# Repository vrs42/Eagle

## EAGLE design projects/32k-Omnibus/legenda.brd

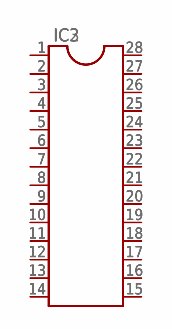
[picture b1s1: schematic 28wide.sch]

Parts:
IC2: DIL28; DIL28-6
IC3: DIL28-3

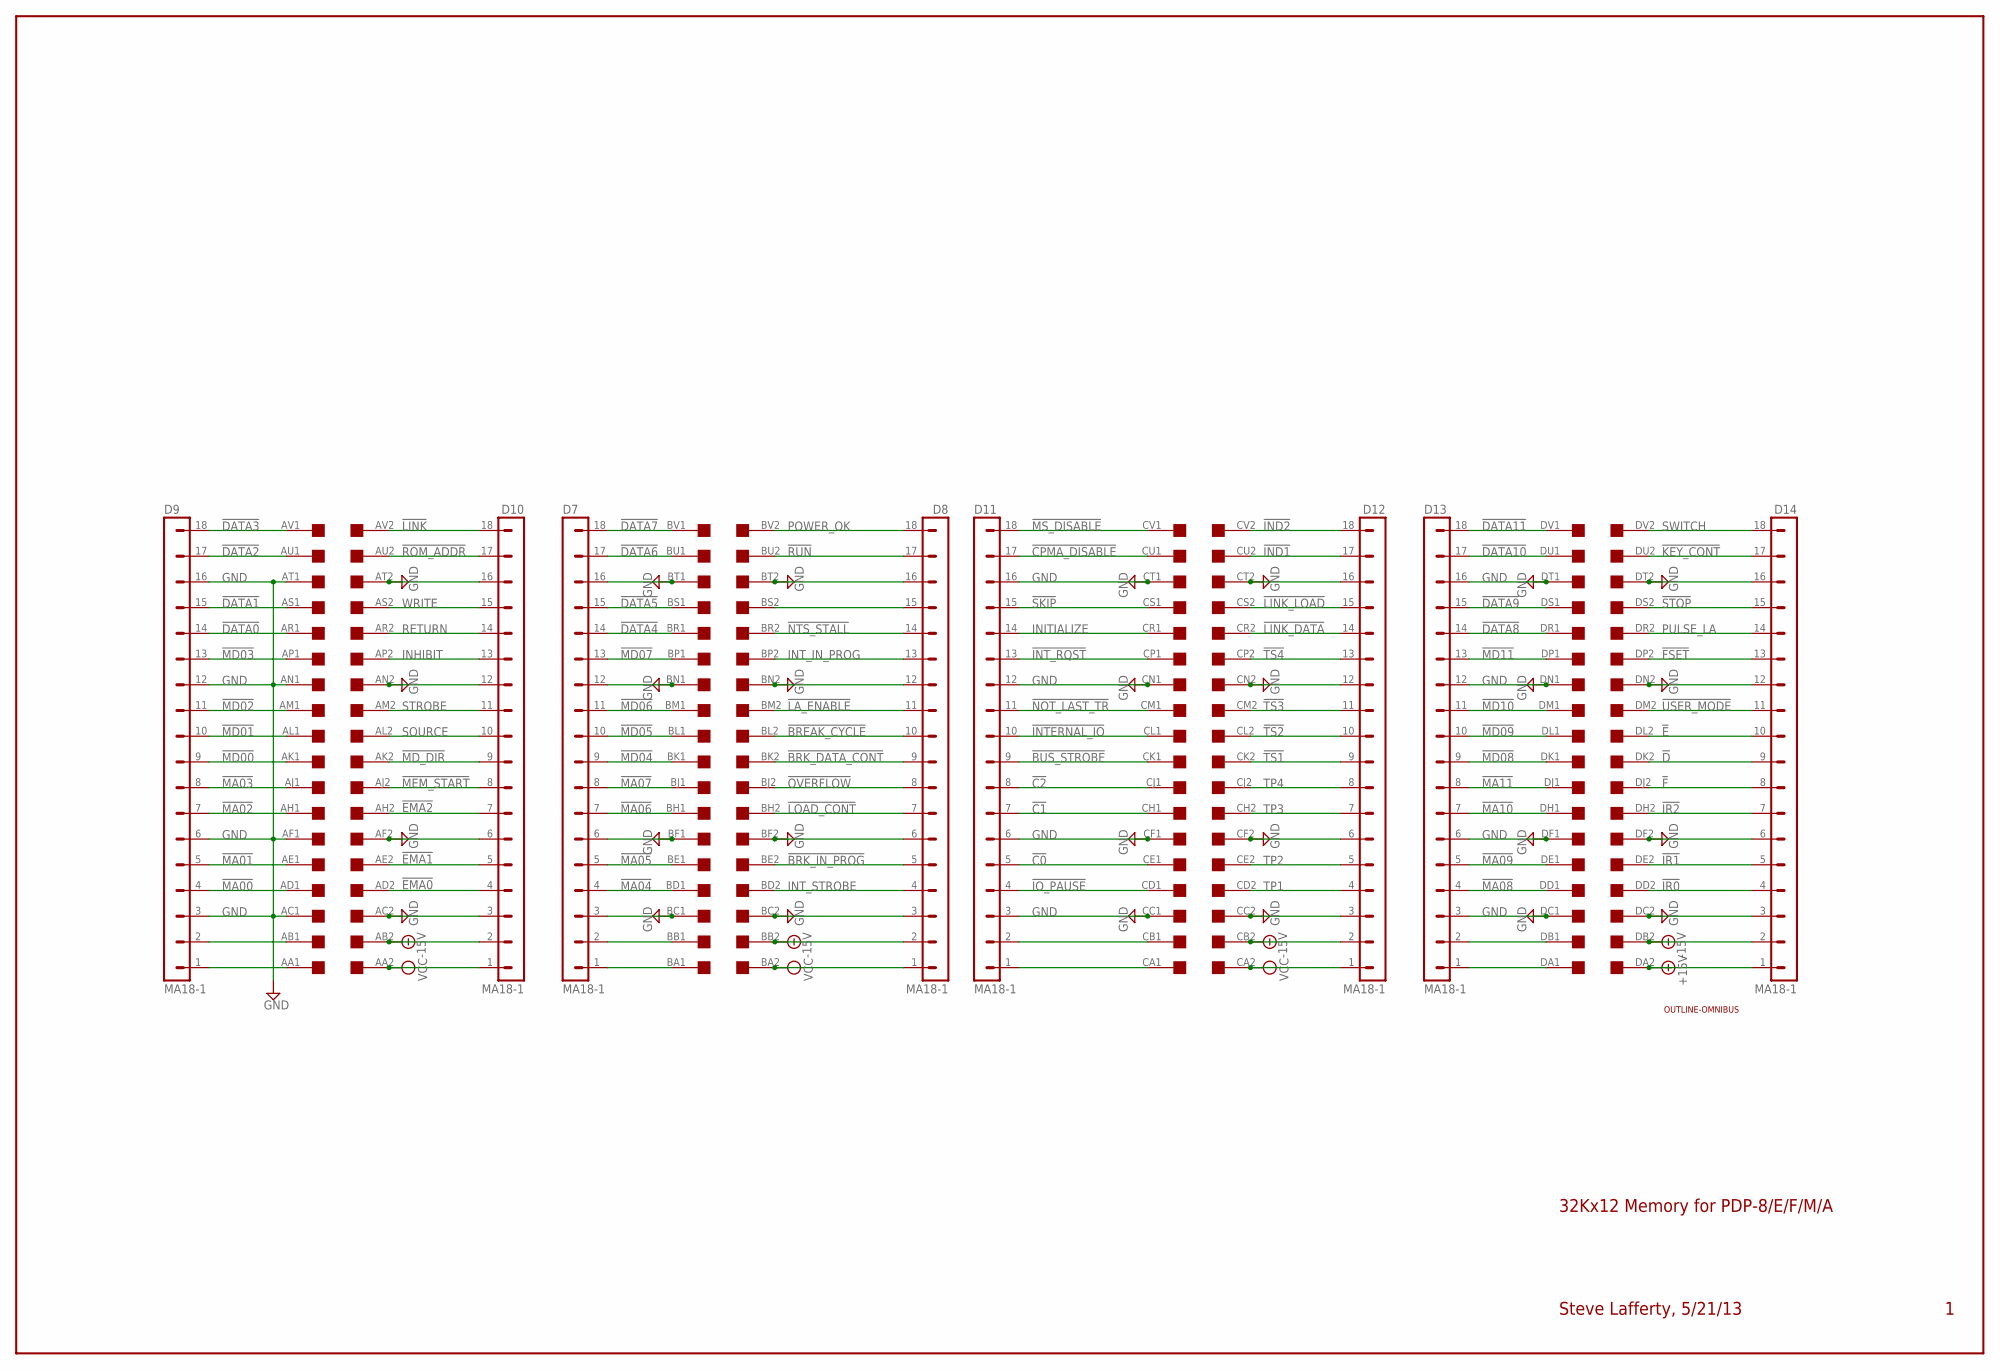
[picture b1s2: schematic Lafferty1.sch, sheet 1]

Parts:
D7, D8, D9, D10, D11, D12, D13, D14: MA18-1
U$1: OUTLINE-OMNIBUS; OMNIBUS
U$2: QUAD; EDGE-CON8

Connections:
!BREAK_CYCLE: D8.10, U$2.BL2
!BRK_DATA_CONT: D8.9, U$2.BK2
!BRK_IN_PROG: D8.5, U$2.BE2
!BUS_STROBE: D11.9, U$2.CK1
!C0: D11.5, U$2.CE1
!C1: D11.7, U$2.CH1
!C2: D11.8, U$2.CJ1
!CPMA_DISABLE: D11.17, U$2.CU1
!D: D14.9, U$2.DK2
!DATA0: D9.14, U$2.AR1
!DATA1: D9.15, U$2.AS1
!DATA2: D9.17, U$2.AU1
!DATA3: D9.18, U$2.AV1
!DATA4: D7.14, U$2.BR1
!DATA5: D7.15, U$2.BS1
!DATA6: D7.17, U$2.BU1
!DATA7: D7.18, U$2.BV1
!DATA8: D13.14, U$2.DR1
!DATA9: D13.15, U$2.DS1
!DATA10: D13.17, U$2.DU1
!DATA11: D13.18, U$2.DV1
!E: D14.10, U$2.DL2
!F: D14.8, U$2.DJ2
!FSET: D14.13, U$2.DP2
!IND1: D12.17, U$2.CU2
!IND2: D12.18, U$2.CV2
!INTERNAL_IO: D11.10, U$2.CL1
!INT_RQST: D11.13, U$2.CP1
!IO_PAUSE: D11.4, U$2.CD1
!IR0: D14.4, U$2.DD2
!IR1: D14.5, U$2.DE2
!IR2: D14.7, U$2.DH2
!KEY_CONT: D14.17, U$2.DU2
!LA_ENABLE: D8.11, U$2.BM2
!LINK: D10.18, U$2.AV2
!LINK_DATA: D12.14, U$2.CR2
!LINK_LOAD: D12.15, U$2.CS2
!LOAD_CONT: D8.7, U$2.BH2
!MD00: D9.9, U$2.AK1; also elsewhere on the board
!MD01: D9.10, U$2.AL1; also elsewhere on the board
!MD02: D9.11, U$2.AM1; also elsewhere on the board
!MD03: D9.13, U$2.AP1; also elsewhere on the board
!MD04: D7.9, U$2.BK1; also elsewhere on the board
!MD05: D7.10, U$2.BL1; also elsewhere on the board
!MD06: D7.11, U$2.BM1; also elsewhere on the board
!MD07: D7.13, U$2.BP1; also elsewhere on the board
!MD_DIR: D10.9, U$2.AK2; also elsewhere on the board
!MEM_START: D10.8, U$2.AJ2
!MS_DISABLE: D11.18, U$2.CV1
!NOT_LAST_TR: D11.11, U$2.CM1
!NTS_STALL: D8.14, U$2.BR2
!OVERFLOW: D8.8, U$2.BJ2
!ROM_ADDR: D10.17, U$2.AU2; also elsewhere on the board
!RUN: D8.17, U$2.BU2
!SKIP: D11.15, U$2.CS1
!STOP: D14.15, U$2.DS2
!TS1: D12.9, U$2.CK2
!TS2: D12.10, U$2.CL2
!TS3: D12.11, U$2.CM2
!TS4: D12.13, U$2.CP2
!USER_MODE: D14.11, U$2.DM2
+15V: D14.1, U$2.DA2
-15V: D8.2, D10.2, D12.2, D14.2, U$2.AB2, U$2.BB2, U$2.CB2, U$2.DB2
INHIBIT: D10.13, U$2.AP2
INITIALIZE: D11.14, U$2.CR1
INT_IN_PROG: D8.13, U$2.BP2
INT_STROBE: D8.4, U$2.BD2
unnamed: D9.2, U$2.AB1
unnamed: D9.1, U$2.AA1
unnamed: D7.2, U$2.BB1
unnamed: D7.1, U$2.BA1
unnamed: D11.1, U$2.CA1
unnamed: D8.15, U$2.BS2
unnamed: D11.2, U$2.CB1
unnamed: D13.1, U$2.DA1
unnamed: D13.2, U$2.DB1
POWER_OK: D8.18, U$2.BV2; also elsewhere on the board
PULSE_LA: D14.14, U$2.DR2
RETURN: D10.14, U$2.AR2
SOURCE: D10.10, U$2.AL2; also elsewhere on the board
STROBE: D10.11, U$2.AM2
SWITCH: D14.18, U$2.DV2
TP1: D12.4, U$2.CD2
TP2: D12.5, U$2.CE2
TP3: D12.7, U$2.CH2
TP4: D12.8, U$2.CJ2
WRITE: D10.15, U$2.AS2; also elsewhere on the board

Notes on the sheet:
32Kx12 Memory for PDP-8/E/F/M/A
Steve Lafferty, 5/21/13

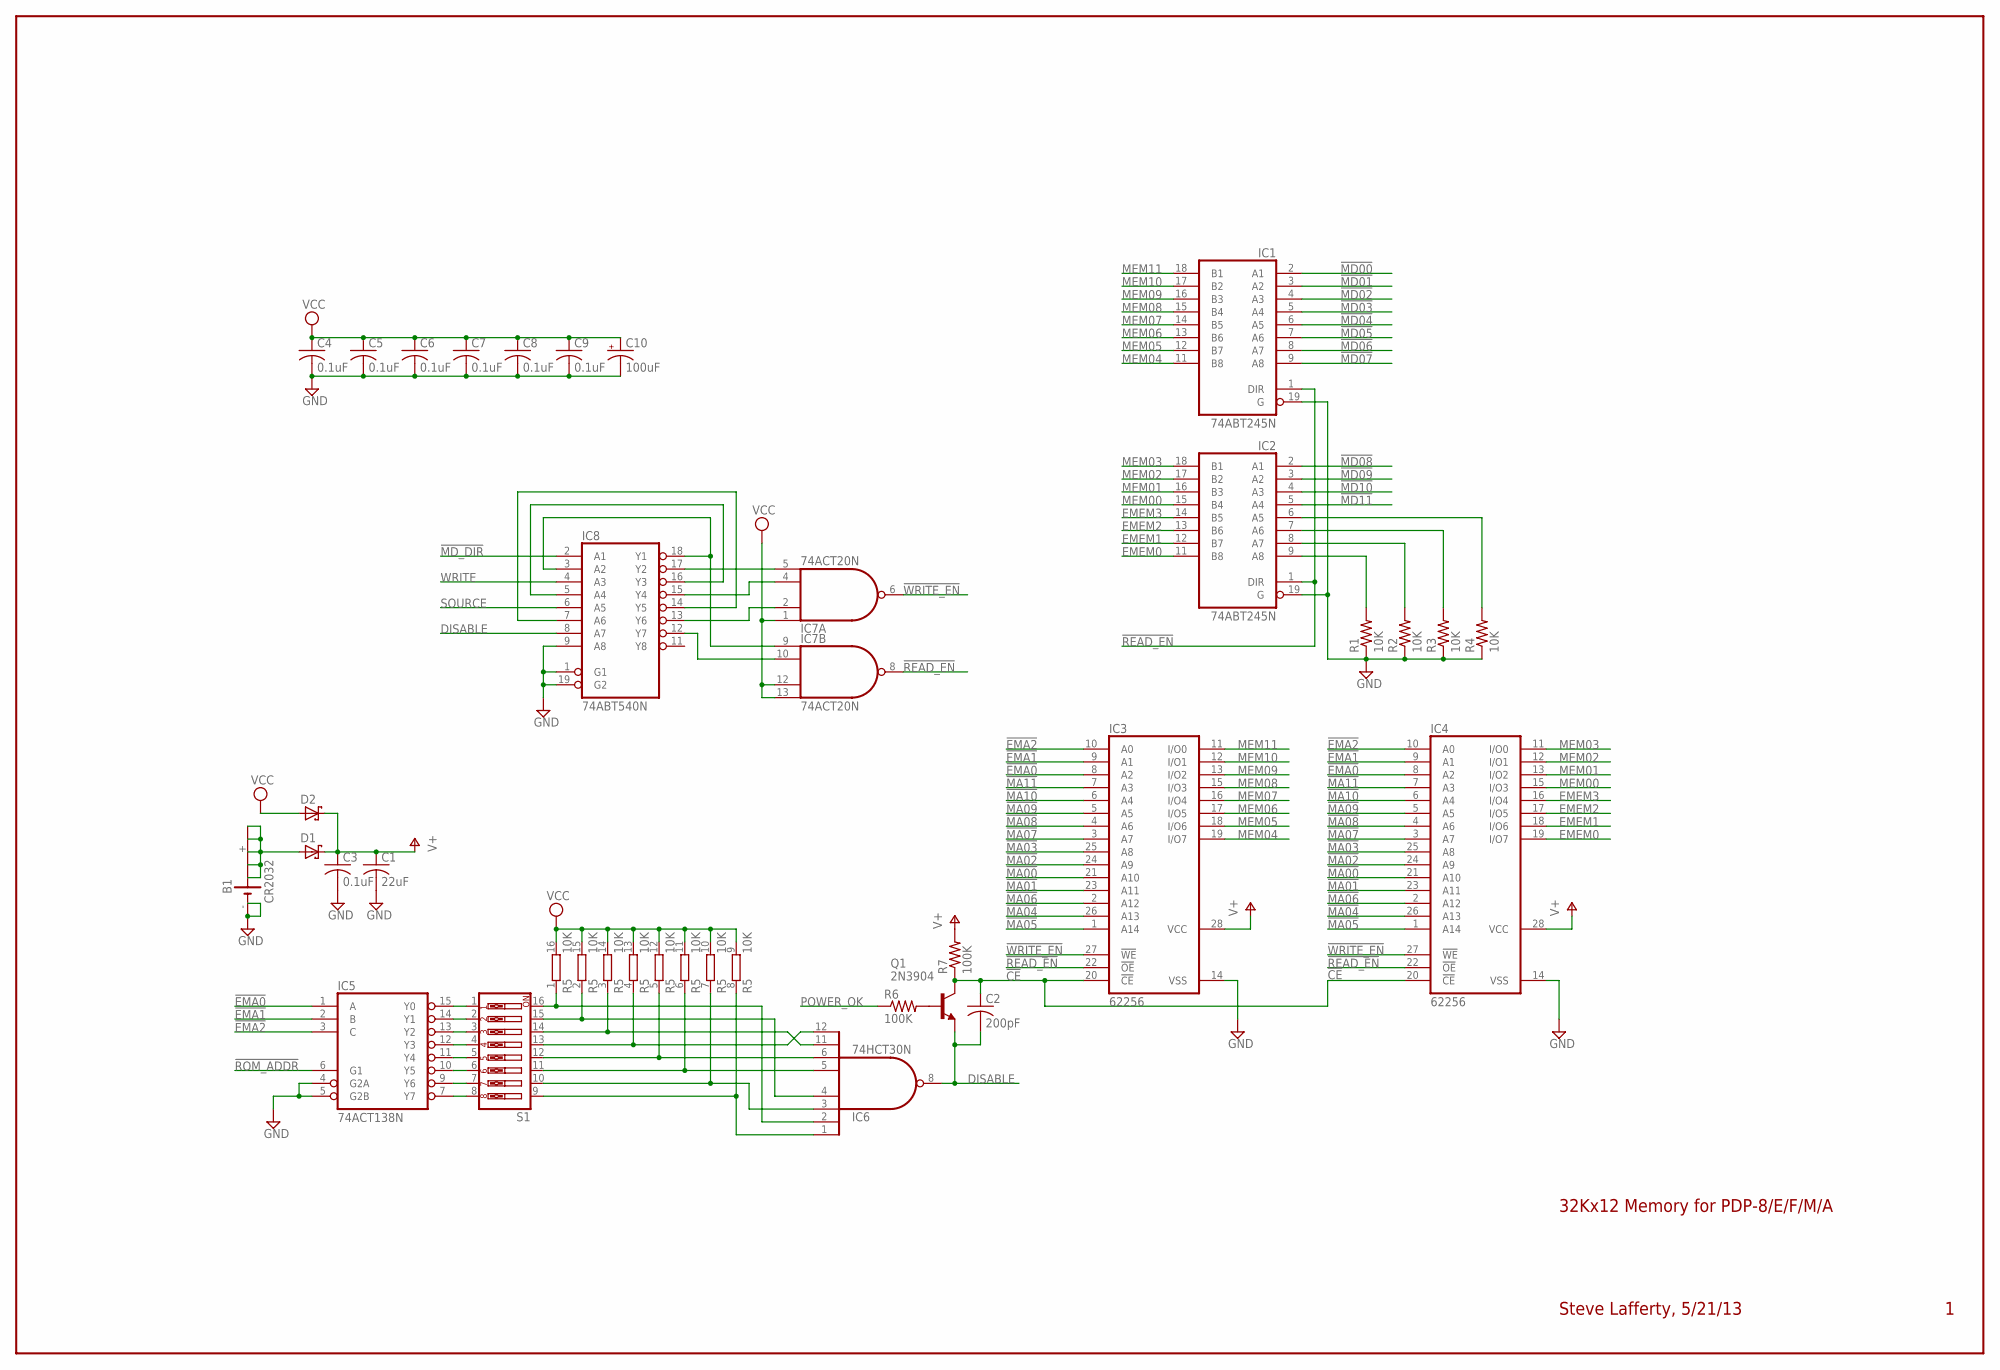
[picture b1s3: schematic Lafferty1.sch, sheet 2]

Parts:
B1: CR2032; B2430UNI
C1: 22uF; C050-025X075
C2: 200pF; C050-025X075
C3, C4, C5, C6, C7, C8, C9: 0.1uF; C050-025X075
C10: 100uF; E12-8
D1, D2: BAT19; DO35-10
IC1, IC2: 74ABT245N; DIL20
IC3, IC4: 62256; DIL28-6
IC5: 74ACT138N; DIL16
IC6: 74HCT30N; DIL14
IC7: 74ACT20N; DIL14
IC8: 74ABT540N; DIL20
Q1: 2N3904; TO92
R1, R2, R3, R4: 10K; 0207/10
R5: 10K; DIL16
R6, R7: 100K; 0207/10
S1: SW_DIP-8; EDG-08

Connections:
!MD00: IC1.2 (A1); also elsewhere on the board
!MD01: IC1.3 (A2); also elsewhere on the board
!MD02: IC1.4 (A3); also elsewhere on the board
!MD03: IC1.5 (A4); also elsewhere on the board
!MD04: IC1.6 (A5); also elsewhere on the board
!MD05: IC1.7 (A6); also elsewhere on the board
!MD06: IC1.8 (A7); also elsewhere on the board
!MD07: IC1.9 (A8); also elsewhere on the board
!MD_DIR: IC8.2 (A1); also elsewhere on the board
!ROM_ADDR: IC5.6 (G1); also elsewhere on the board
DISABLE: C2.2, IC6.8 (O), IC8.8 (A7), Q1.3 (E)
unnamed: B1.+, B1.+@1 (+), B1.+@2 (+), B1.+@3 (+), B1.+@4 (+), D1.A
unnamed: IC7.5 (I3), IC8.17 (Y2)
unnamed: Q1.2 (B), R6.2
unnamed: IC8.5 (A4), IC8.16 (Y3)
unnamed: IC7.9 (I0), IC8.3 (A2), IC8.18 (Y1)
unnamed: IC8.7 (A6), IC8.14 (Y5)
unnamed: IC7.2 (I1), IC8.13 (Y6)
unnamed: IC7.4 (I2), IC8.15 (Y4)
unnamed: IC7.10 (I1), IC8.12 (Y7)
POWER_OK: R6.1; also elsewhere on the board
SOURCE: IC8.6 (A5); also elsewhere on the board
WRITE: IC8.4 (A3); also elsewhere on the board

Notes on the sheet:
32Kx12 Memory for PDP-8/E/F/M/A
Steve Lafferty, 5/21/13

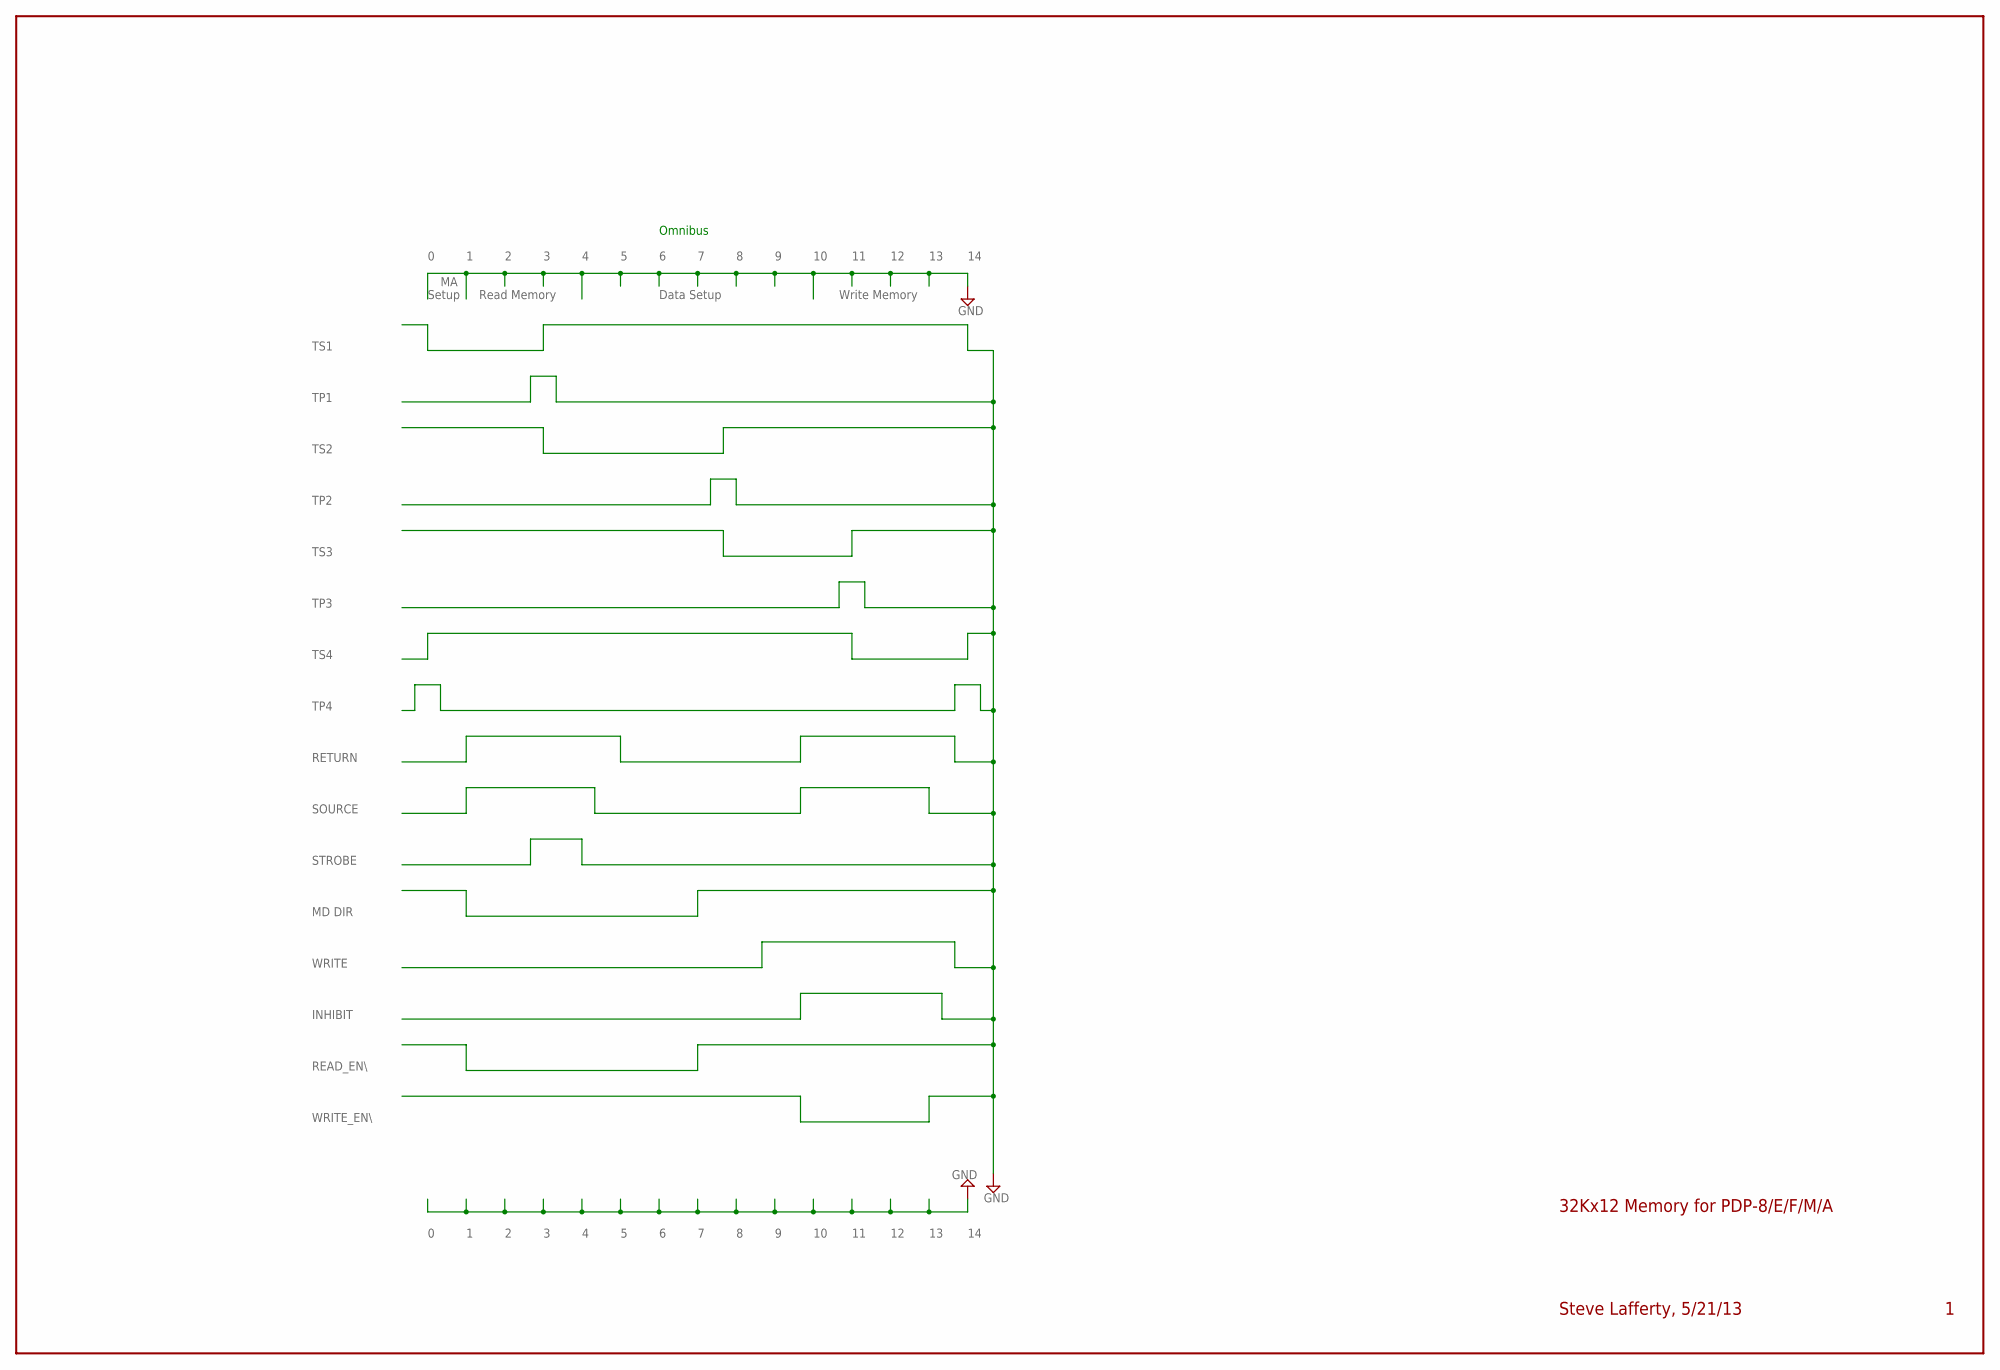
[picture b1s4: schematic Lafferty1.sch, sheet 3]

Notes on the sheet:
TS1
TS2
TS3
TS4
TP1
TP2
TP3
TP4
INHIBIT
WRITE
STROBE
SOURCE
RETURN
MD DIR
Setup
Read Memory
Data Setup
Write Memory
Omnibus
READ_EN\\
WRITE_EN\\
32Kx12 Memory for PDP-8/E/F/M/A
Steve Lafferty, 5/21/13
